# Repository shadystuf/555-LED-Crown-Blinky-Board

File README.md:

# 555-LED-Crown-Blinky-Board
I made this project based on one of the STASIS starter projects in a Hackclub workshop in St. Clare's, Oxford lead by Caterina. This was a great opportunity to understand how computers work, so I took it. This is my very first prject, so I wanted to start on something easier, like a blinky board. It was still quite difficult. 
This is the 3d model of my project

This is my PCB with wiring 

This is my schematics/wiring diagram

This is my BOM screenshot

BOM:
Timer IC --> NEE555P
IC to Control LEDs --> CD4017
Various values --> Resistors
Various values --> Capacitors
9x --> LEDs

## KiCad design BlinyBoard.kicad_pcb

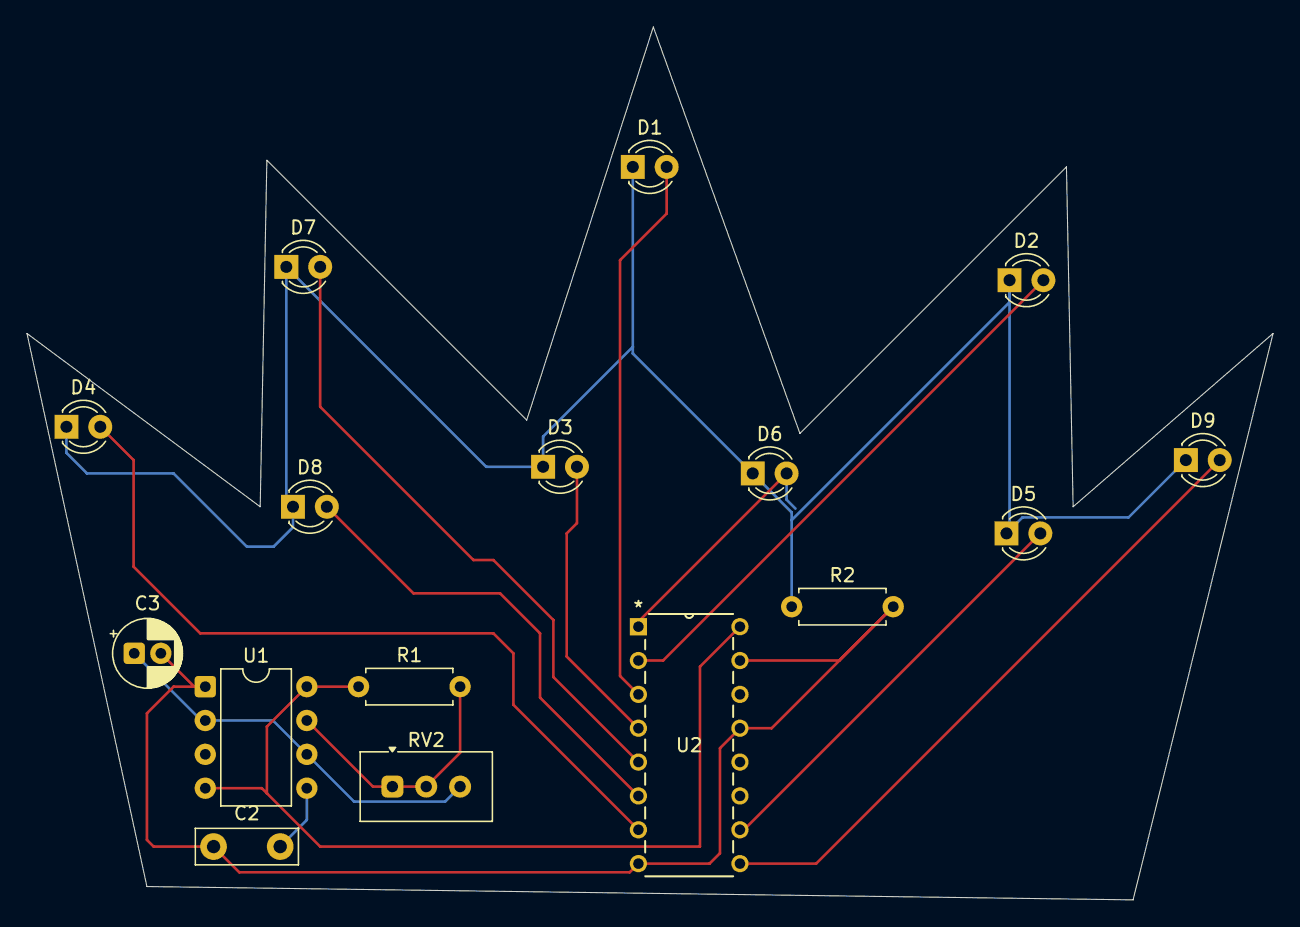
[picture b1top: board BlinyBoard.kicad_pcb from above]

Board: 2 copper layers, 93.5 x 65.5 mm, 16 parts (0 on the bottom side), 15 nets.

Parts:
C2: 0.01uF; C_Disc_D7.5mm_W2.5mm_P5.00mm
C3: 1uF; CP_Radial_D5.0mm_P2.00mm
D1, D2, D3, D4, D5, D6, D7, D8, D9: LED; LED_D3.0mm
R1: 1k; R_Axial_DIN0207_L6.3mm_D2.5mm_P7.62mm_Horizontal
R2: 470; R_Axial_DIN0207_L6.3mm_D2.5mm_P7.62mm_Horizontal
RV2: 50k; Potentiometer_Vishay_T93YA_Vertical
U1: NE555P; DIP-8_W7.62mm
U2: 4017; N16

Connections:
+5V: R1.1, U1.4 (~RST), U1.8 (VCC), U2.16 (VDD)
GND: C2.1, C3.2, R2.2, U1.1 (GND), U2.8 (VSS), U2.13 (CKEN), U2.15 (Reset)
unnamed: D1.2 (A), U2.3 (Q0)
unnamed: D1.1 (K), D2.1 (K), D3.1 (K), D4.1 (K), D5.1 (K), D6.1 (K), D7.1 (K), D8.1 (K), D9.1 (K), R2.1
unnamed: D2.2 (A), U2.2 (Q1)
unnamed: D3.2 (A), U2.4 (Q2)
unnamed: D4.2 (A), U2.7 (Q3)
unnamed: D5.2 (A), U2.10 (Q4)
unnamed: D6.2 (A), U2.1 (Q5)
unnamed: D7.2 (A), U2.5 (Q6)
unnamed: D8.2 (A), U2.6 (Q7)
unnamed: D9.2 (A), U2.9 (Q8)
unnamed: C2.2, U1.5 (CONT)
unnamed: R1.2, RV2.1, RV2.2, U1.7 (DISCH)
TR: C3.1, RV2.3, U1.2 (TRIG), U1.6 (THRES)

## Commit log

2026-04-16 3D view screenshot
2026-04-16 Blinky Board Schematic
2026-04-16 Blinky Board PCB
2026-04-16 Blinky Board Project
2026-04-16 Blinky Board Gerber Files
2026-04-16 Update README.md
    Added a description and screenshot
2026-04-16 Update README.md
    Added pictures and BOM
2026-04-17 3D model of Crown Blinky Board
